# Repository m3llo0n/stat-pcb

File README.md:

# stat-pcb

Schematic and PCB layout for the Student Tech Against Trafficking (STAT) project

Code will be found in another repository (I think maybe, ask @m3llo0n)

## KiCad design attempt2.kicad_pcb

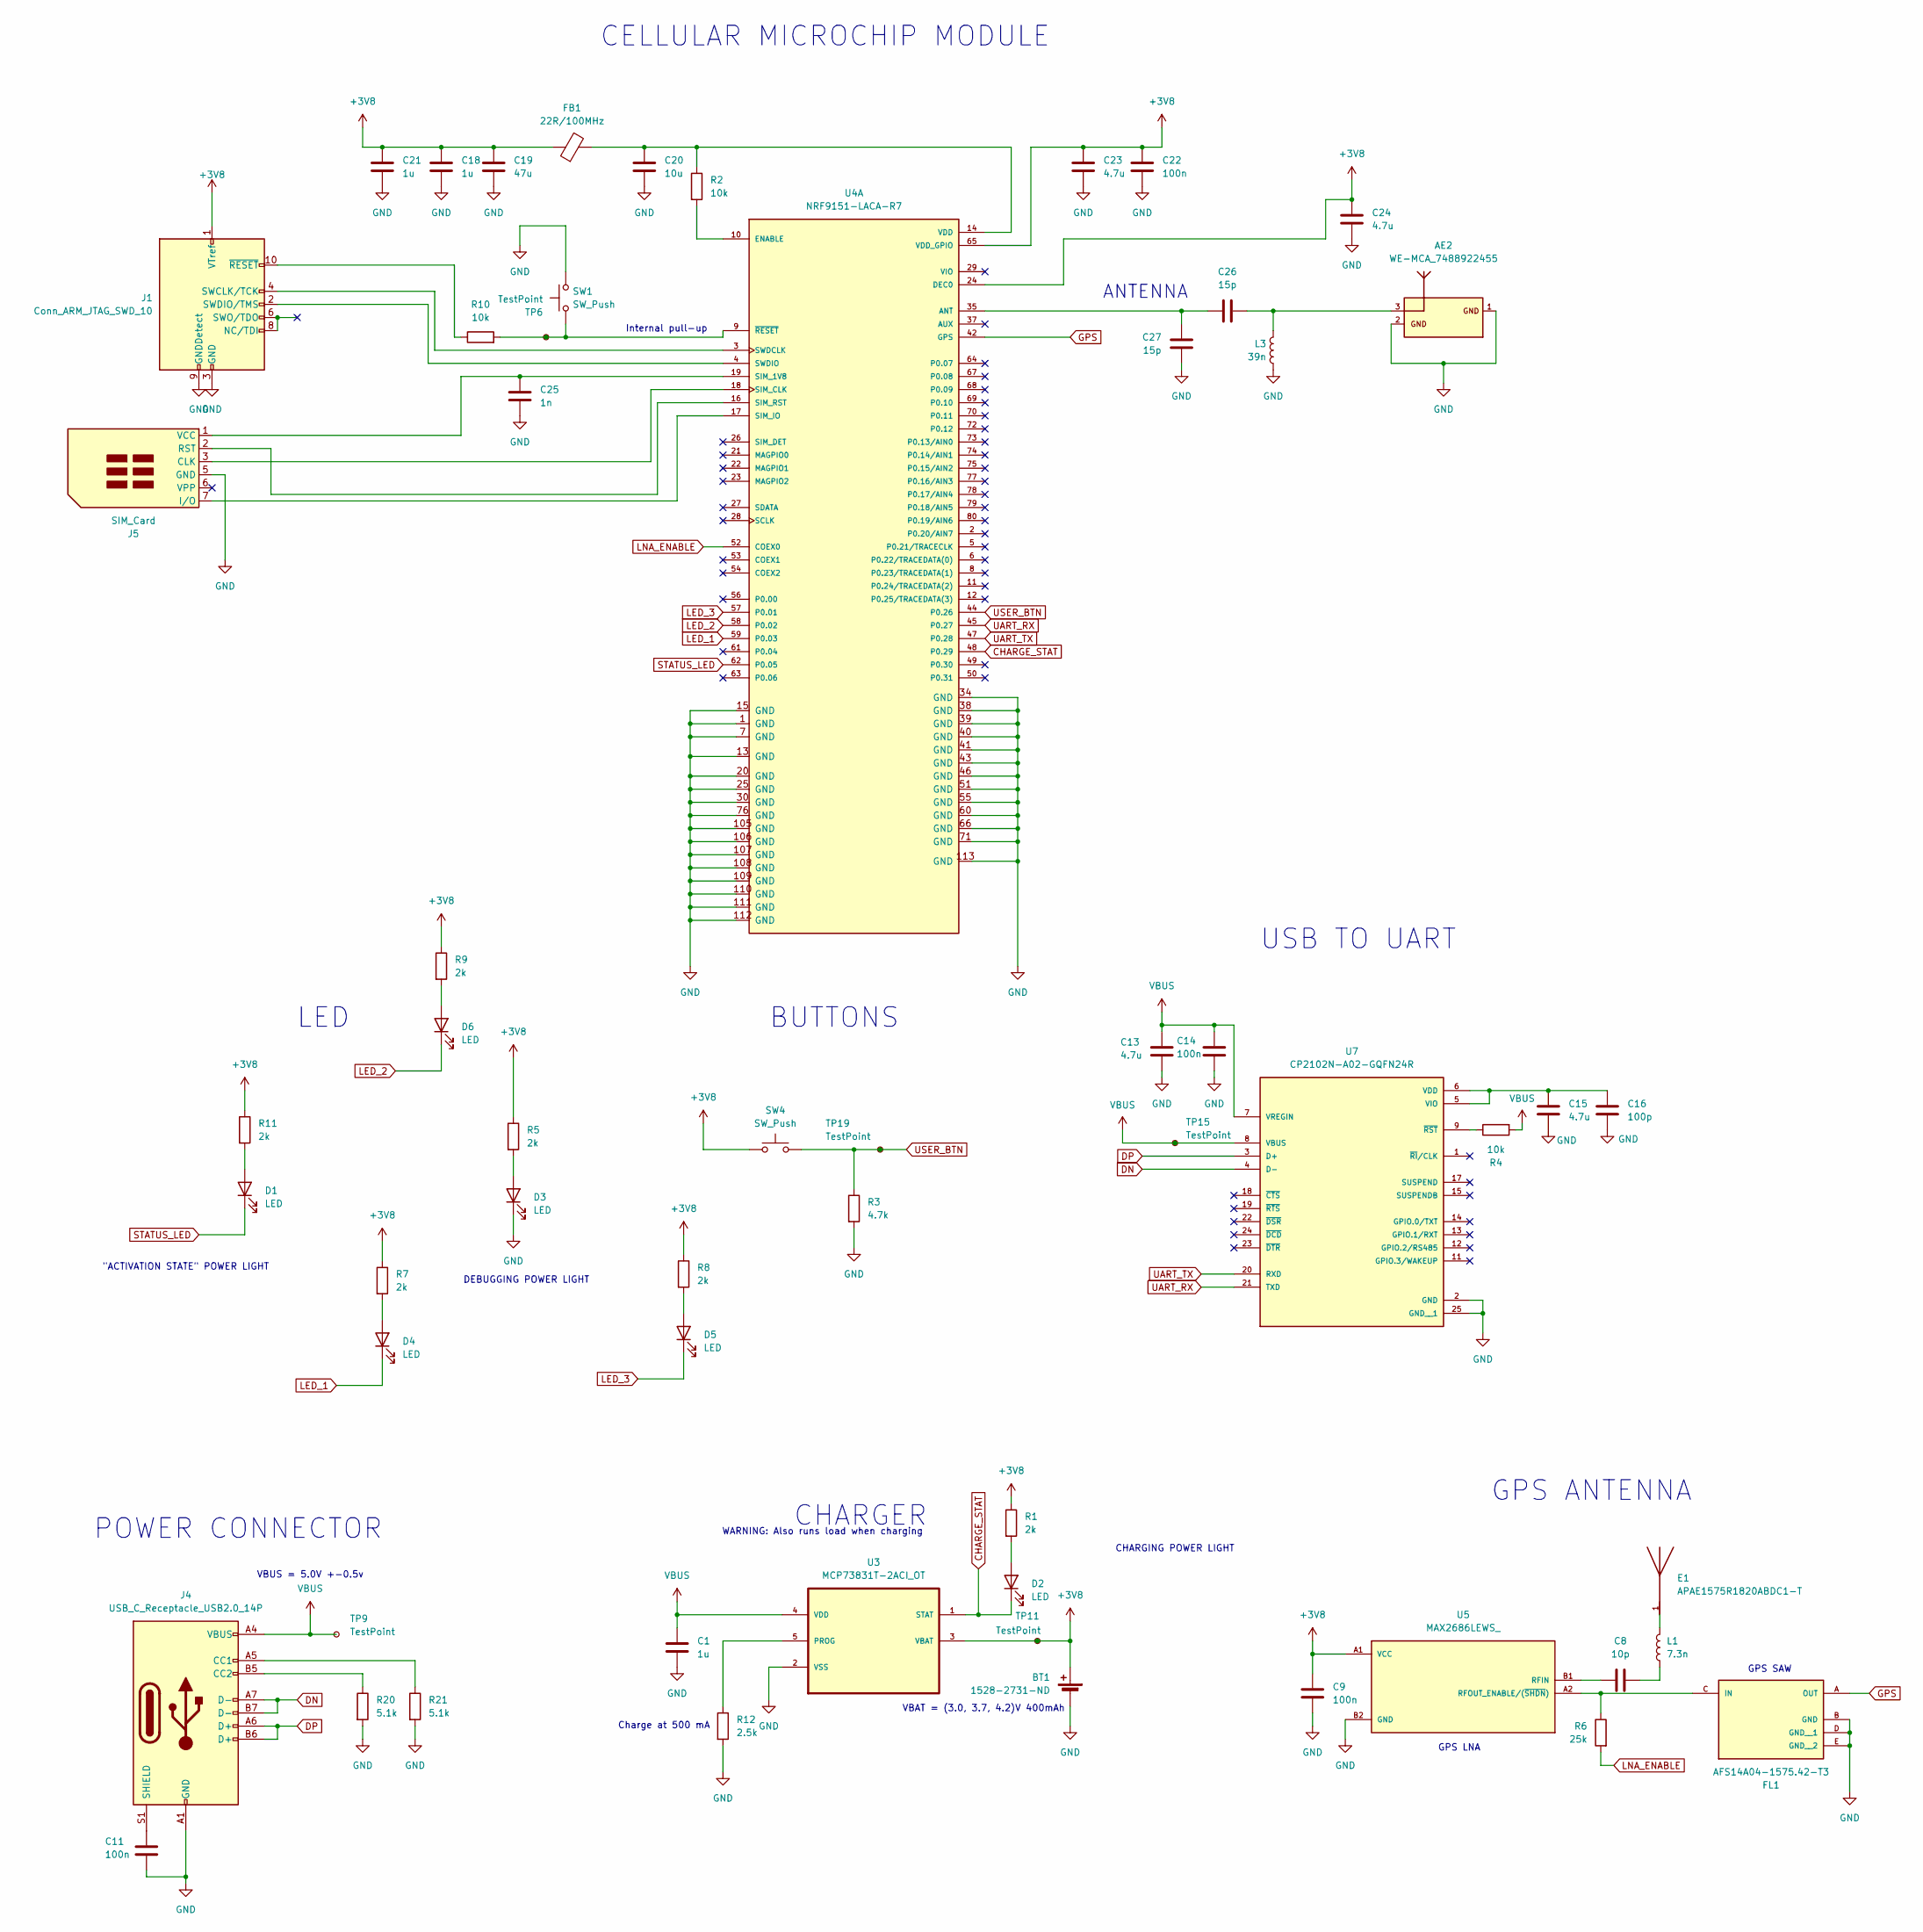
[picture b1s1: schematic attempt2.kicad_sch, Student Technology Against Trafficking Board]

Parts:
AE2: WE-MCA_7488922455; Digikey PN 7488922455
BT1: 1528-2731-ND; JST_PHR-2; Digikey PN 2073-USB4110-GF-A-1-ND
C1, C18, C21: 1u; C_0603_1608Metric; Digikey PN 587-3247-1-ND
C8: 10p; C_0603_1608Metric; Digikey PN 399-C0603C100J5GACTUCT-ND
C9, C22: 100n; C_0603_1608Metric; Digikey PN 311-1069-1-ND
C11, C14: 100n; C_0603_1608Metric; Digikey PN 311-1088-1-ND
C13, C15, C24: 4.7u; C_0603_1608Metric; Digikey PN 490-7203-1-ND
C16: 100p; C_0603_1608Metric; Digikey PN 311-1069-1-ND
C19: 47u; C_0603_1608Metric; Digikey PN 490-13247-1-ND
C20: 10u; C_0603_1608Metric; Digikey PN 587-3258-1-ND
C23: 4.7u; C_0603_1608Metric
C25: 1n; C_0603_1608Metric; Digikey PN 399-C0603C102K5RACTUCT-ND
C26, C27: 15p; C_0603_1608Metric; Digikey PN 478-600S150JT250XT4KCT-ND
D1, D3: LED; LED_1206_3216Metric; Digikey PN 3147-T1341NB--30C000112U1930CT-ND
D2: LED; LED_1206_3216Metric; Digikey PN 3147-T1341MND-20P000312U1930CT-ND
D4, D5: LED; LED_1206_3216Metric; Digikey PN 3147-B1591UD--20C000112U1930CT-ND
D6: LED; LED_1206_3216Metric
E1: APAE1575R1820ABDC1-T; XDCR_APAE1575R1820ABDC1-T; Digikey PN 535-11944-ND
FB1: 22R/100MHz; L_Eaton_MCL2012V1; Digikey PN 490-5246-1-ND
FL1: AFS14A04-1575.42-T3; FIL_AFS14A04-1575.42-T3; PARTREV 04.16.13; Digikey PN 535-12060-1-ND
J1: Conn_ARM_JTAG_SWD_10; PinSocket_2x05_P2.54mm_Vertical_SMD; Digikey PN S5675-ND
J4: USB_C_Receptacle_USB2.0_14P; USB_C_Receptacle_GCT_USB4110; Digikey PN USB4110-GF-A
J5: SIM_Card; nanoSIM_GCT_SIM8060-6-0-14-00; Digikey PN 2073-SIM8060-6-1-14-00-ACT-ND
L1: 7.3n; L_0603_1608Metric; Digikey PN 3442-SDWL1608CP7N2JSTFCT-ND
L3: 39n; L_0603_1608Metric; Digikey PN 712-LRC0603CJ39NGV001TCT-ND
R1, R5, R7, R8, R9, R11: 2k; R_0603_1608Metric; Digikey PN P2.0KDBCT-ND
R2, R4, R10: 10k; R_0603_1608Metric; Digikey PN 311-10.0KHRCT-ND
R3: 4.7k; R_0603_1608Metric; Digikey PN 311-4.70KHRCT-ND
R6: 25k; R_0603_1608Metric; Digikey PN PLT0603-25KACT-ND
R12: 2.5k; R_0603_1608Metric; Digikey PN 738-RNCF0603BTE2K50CT-ND
R20, R21: 5.1k; R_0603_1608Metric; Digikey PN 311-5.10KHRCT-ND
SW1: SW_Push; SW_Push_1P1T_NO_CK_KMR2; Digikey PN 141-TL2233OACT-ND
SW4: SW_Push; SW_Push_1P1T_NO_CK_KSC6xxJ; Digikey PN 141-TL2233OACT-ND
TP6, TP9, TP11, TP15, TP19: TestPoint; TestPoint_Pad_D2.0mm
U3: MCP73831T-2ACI_OT; SOT95P280X145-5N; MPN MCP73831T-2ACI/OT; Digikey PN MCP73831T-2ACI/OTCT-ND
U4: NRF9151-LACA-R7; XCVR_NRF9151-LACA-R7; PARTREV 1.0; Digikey PN 4823-NRF9151-LACA-R7CT-ND
U5: MAX2686LEWS_; BGA4N40P2X2_84X84X69N; Digikey PN 175-MAX2686LEWS+TCT-ND
U7: CP2102N-A02-GQFN24R; QFN50P400X400X80-25N; PARTREV 1.3; Digikey PN CP2102N-A02-GQFN24R

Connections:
+3V8: BT1.1 (+), C9.1, C18.1, C19.1, C21.1, C22.1, C23.1, C24.1, FB1.1, J1.1 (VTref), R1.1, R5.1, R7.1, R8.1, R9.1, R11.1, SW4.1, TP11.1, U3.3 (VBAT), U4.24 (DEC0), U4.65 (VDD_GPIO), U5.A1 (VCC)
CHARGE_STAT: D2.1 (K), U3.1 (STAT), U4.48 (P0.29)
DN: J4.A7 (D-), J4.B7 (D-), U7.4 (D-)
DP: J4.A6 (D+), J4.B6 (D+), U7.3 (D+)
GND: AE2.1, AE2.2, BT1.2 (-), C1.2, C9.2, C11.2, C13.2, C14.2, C15.2, C16.2, C18.2, C19.2, C20.2, C21.2, C22.2, C23.2, C24.2, C25.2, C27.2, D3.1 (K), FL1.B (GND), FL1.D (GND__1), FL1.E (GND__2), J1.3 (GND), J1.5 (GND), J1.9 (GNDDetect), J4.A1 (GND), J4.A12 (GND), J4.B1 (GND), J4.B12 (GND), J5.5 (GND), L3.2, R3.2, R12.2, R20.2, R21.2, SW1.2, U3.2 (VSS), U4.1 (GND), U4.7 (GND), U4.13 (GND), U4.15 (GND), U4.20 (GND), U4.25 (GND), U4.30 (GND), U4.34 (GND), U4.38 (GND), U4.39 (GND), U4.40 (GND), U4.41 (GND), U4.43 (GND), U4.46 (GND), U4.51 (GND), U4.55 (GND), U4.60 (GND), U4.66 (GND), U4.71 (GND), U4.76 (GND), U4.105 (GND), U4.106 (GND), U4.107 (GND), U4.108 (GND), U4.109 (GND), U4.110 (GND), U4.111 (GND), U4.112 (GND), U4.113 (GND), U5.B2 (GND), U7.2 (GND), U7.25 (GND__1)
GPS: FL1.A (OUT), U4.42 (GPS)
LED_1: D4.1 (K), U4.59 (P0.03)
LED_2: D6.1 (K), U4.58 (P0.02)
LED_3: D5.1 (K), U4.57 (P0.01)
LNA_ENABLE: R6.2, U4.52 (COEX0)
unnamed: AE2.3, C26.1, L3.1
unnamed: C8.1, L1.1
unnamed: D1.2 (A), R11.2
unnamed: D2.2 (A), R1.2
unnamed: D3.2 (A), R5.2
unnamed: D4.2 (A), R7.2
unnamed: D5.2 (A), R8.2
unnamed: D6.2 (A), R9.2
unnamed: E1.1, L1.2
unnamed: FL1.C (IN), R6.1, U5.A2 (RFOUT_ENABLE/(~SHDN))
unnamed: J1.4 (SWCLK/TCK), U4.3 (SWDCLK)
unnamed: J1.2 (SWDIO/TMS), U4.4 (SWDIO)
unnamed: J1.10 (~RESET), R10.1
unnamed: J4.A5 (CC1), R21.1
unnamed: J4.B5 (CC2), R20.1
unnamed: C11.1, J4.S1 (SHIELD)
unnamed: J5.3 (CLK), U4.18 (SIM_CLK)
unnamed: J5.7 (I/O), U4.17 (SIM_IO)
unnamed: J5.2 (RST), U4.16 (SIM_RST)
unnamed: C25.1, J5.1 (VCC), U4.19 (SIM_1V8)
unnamed: R12.1, U3.5 (PROG)
unnamed: C26.2, C27.1, U4.35 (ANT)
unnamed: R2.2, U4.10 (ENABLE)
unnamed: C20.1, FB1.2, R2.1, U4.14 (VDD)
unnamed: R10.2, SW1.1, TP6.1, U4.9 (~RESET)
unnamed: C8.2, U5.B1 (RFIN)
unnamed: C15.1, C16.1, U7.5 (VIO), U7.6 (VDD)
unnamed: R4.1, U7.9 (~RST)
STATUS_LED: D1.1 (K), U4.62 (P0.05)
UART_RX: U4.45 (P0.27), U7.21 (TXD)
UART_TX: U4.47 (P0.28), U7.20 (RXD)
USER_BTN: R3.1, SW4.2, TP19.1, U4.44 (P0.26)
VBUS: C1.1, C13.1, C14.1, J4.A4 (VBUS), J4.A9 (VBUS), J4.B4 (VBUS), J4.B9 (VBUS), R4.2, TP9.1, TP15.1, U3.4 (VDD), U7.7 (VREGIN), U7.8 (VBUS)

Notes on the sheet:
GPS LNA
LED
GPS ANTENNA
GPS SAW
Internal pull-up
CHARGING POWER LIGHT
VBUS = 5.0V +-0.5v
ANTENNA
VBAT = (3.0, 3.7, 4.2)V 400mAh
WARNING: Also runs load when charging
BUTTONS
{dblquote}ACTIVATION STATE{dblquote} POWER LIGHT
DEBUGGING POWER LIGHT
CELLULAR MICROCHIP MODULE
CHARGER
USB TO UART
POWER CONNECTOR
Charge at 500 mA

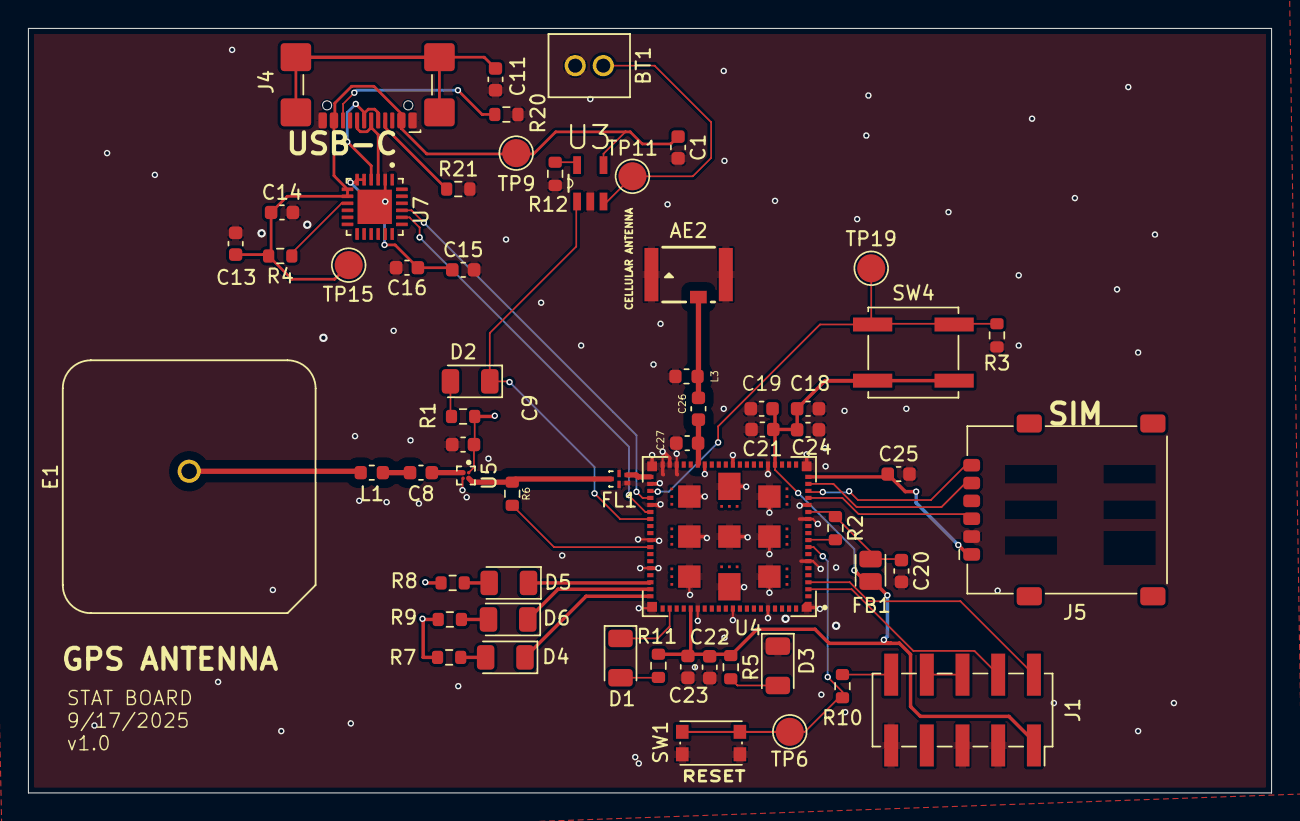
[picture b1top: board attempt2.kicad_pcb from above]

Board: 4 copper layers, 88.5 x 54.4 mm, 59 parts (0 on the bottom side), 43 nets.

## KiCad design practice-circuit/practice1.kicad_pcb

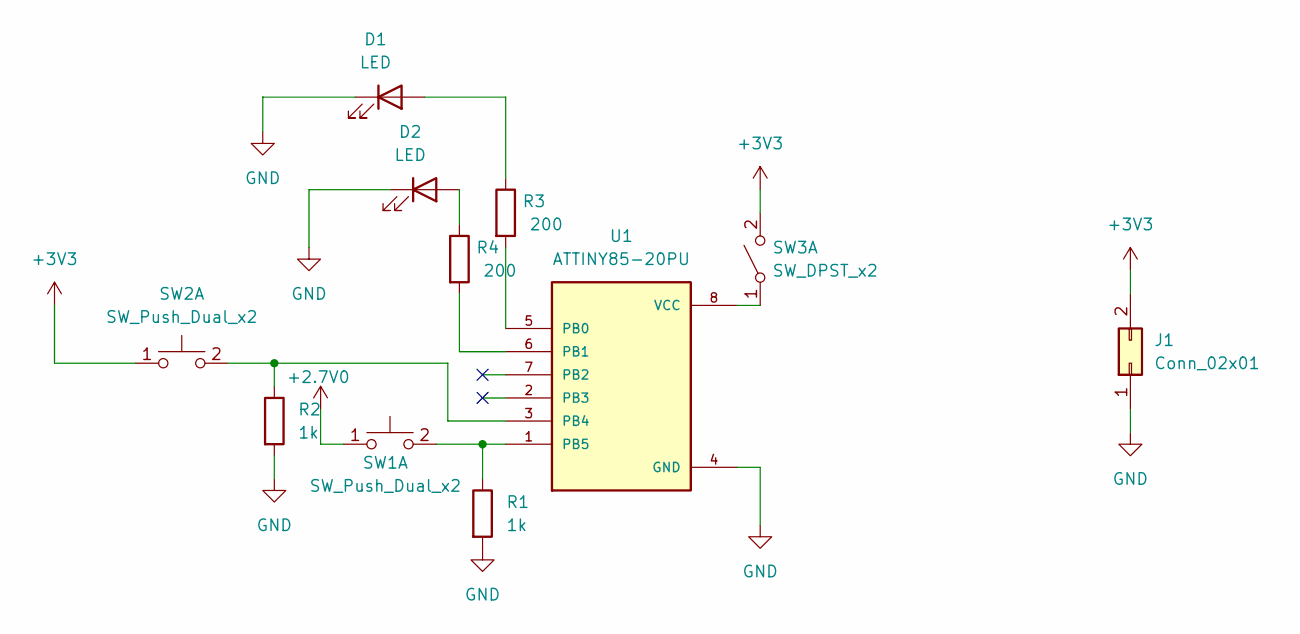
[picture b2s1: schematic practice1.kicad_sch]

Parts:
D1: LED; LED_0201_0603Metric
D2: LED; LED_1206_3216Metric_Pad1.42x1.75mm_HandSolder
J1: Conn_02x01; PinHeader_2x01_P1.27mm_Vertical_SMD
R1, R2: 1k; R_0201_0603Metric
R3: 200; R_0402_1005Metric
R4: 200; R_0201_0603Metric
SW1: SW_Push_Dual_x2; SW_Push_2P1T_Toggle_CK_PVA1xxH1xxxxxxV2
SW2: SW_Push_Dual_x2; SW_Push_2P1T_Toggle_CK_PVA1xxH2xxxxxxV2
SW3: SW_DPST_x2; SW_DIP_SPSTx02_Slide_6.7x6.64mm_W7.62mm_P2.54mm_LowProfile
U1: ATTINY85-20PU; DIP762W46P254L927H533Q8B

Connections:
+2.7V0: SW1.1 (C)
+3V3: J1.2, SW2.1 (C), SW3.2 (B)
GND: D1.1 (K), D2.1 (K), J1.1, R1.2, R2.2, U1.4 (GND)
unnamed: D1.2 (A), R3.1
unnamed: D2.2 (A), R4.1
unnamed: R1.1, SW1.2 (D), U1.1 (PB5)
unnamed: R2.1, SW2.2 (D), U1.3 (PB4)
unnamed: SW3.1 (A), U1.8 (VCC)
unnamed: R3.2, U1.5 (PB0)
unnamed: R4.2, U1.6 (PB1)

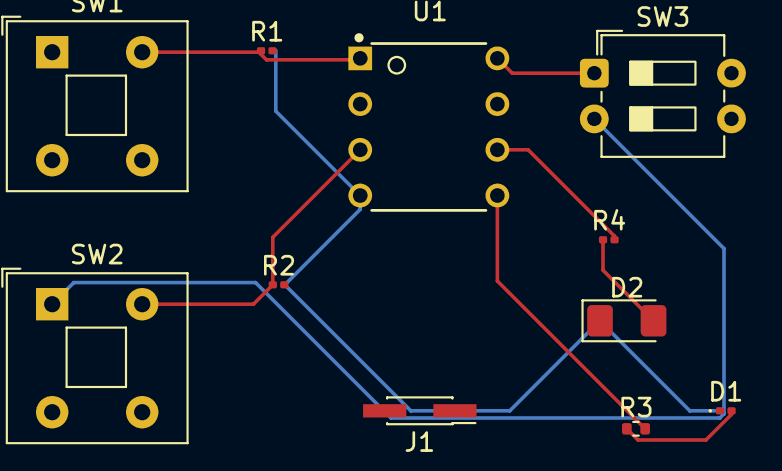
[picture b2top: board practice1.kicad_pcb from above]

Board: 2 copper layers, 11 parts (0 on the bottom side), 9 nets.

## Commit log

2025-07-16 i added more stuff
2025-07-18 yay pt 2
2025-07-18 Cleaned up repository
2025-07-18 i cleaned the sheet
2025-07-22 asdf
2025-07-23 cleaned
2025-07-23 rah i did work on the practice footprint
2025-07-23 i'm adding all of my symbol files in
2025-07-24 asdfklj
2025-07-24 Initial Andrew design review
2025-07-24 all the footprints...
2025-07-24 started work on pcb
2025-07-27 i did pcb wires
2025-07-27 testboard version
    this is what we will use while programming to board.
2025-07-27 added a diode
2025-07-27 wires the other diode
2025-07-27 moved some silkscreens
2025-07-29 changed out antenna and fixed jst battery connector. also edited schematic
2025-07-29 changed the connector to a jst_phr_2
2025-07-30 switched to an esim
2025-07-31 switched in the esim and removed physical card
2025-08-01 flipped direction of usb and moved antennas to edge
2025-08-01 edited exclusions for erc
2025-08-01 worked on erc and drc errors
2025-08-02 final cleanup before design review
2025-08-02 voltage divider fixed
2025-08-02 FINAL BEFORE ANDREW
2025-08-02 fixed resistor values
2025-08-02 added decoupling capacitor to esim vcc
2025-08-02 CLeaned up .gitignore for KiCad 9 and removed PRL file.
2025-08-02 OK .gitignore again, this time on the right branch, and also remove temp files.
2025-08-02 Schematic design review, remove 3.3V switcher and run right off battery, re-arrange schematic for easier reading, moved to four layer PCB because RF, cleaned up zones, including adding vbat zone. Ple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
2025-08-03 changed gps antenna lte antenna xibidi and other thins too
2025-08-03 remade entire pcb for new schematic
2025-08-04 updated gps antenna
2025-08-12 changed nrf9160 to nrf9151
2025-08-13 added silkscreen
2025-08-13 overwrote main with testboard forcibly by saving
2025-08-13 forced the schematic to merge via a copy and paste...
2025-08-14 increased thickness of antenna and power lines. cleaned up silkscreen a little more. added missing capacitor and ferrite bead values. deleted a few useless testpoints
2025-08-15 small things
2025-09-01 moved antennas to be perpendicular to ic and cleaned silkscreen
2025-09-09 i added the flooded ground planes around the gps and cellular antenna
2025-09-12 changed literally everything moved so much.
2025-09-12 added more netclass vals
2025-09-17 moved some ground pins
2025-09-18 worked with andrew on a few adjustments
2025-09-20 changes made with andrew
2025-09-26 unno
2025-10-01 i added digikey info pn
2025-10-02 skibidi
2025-10-12 mmm i messed with files
